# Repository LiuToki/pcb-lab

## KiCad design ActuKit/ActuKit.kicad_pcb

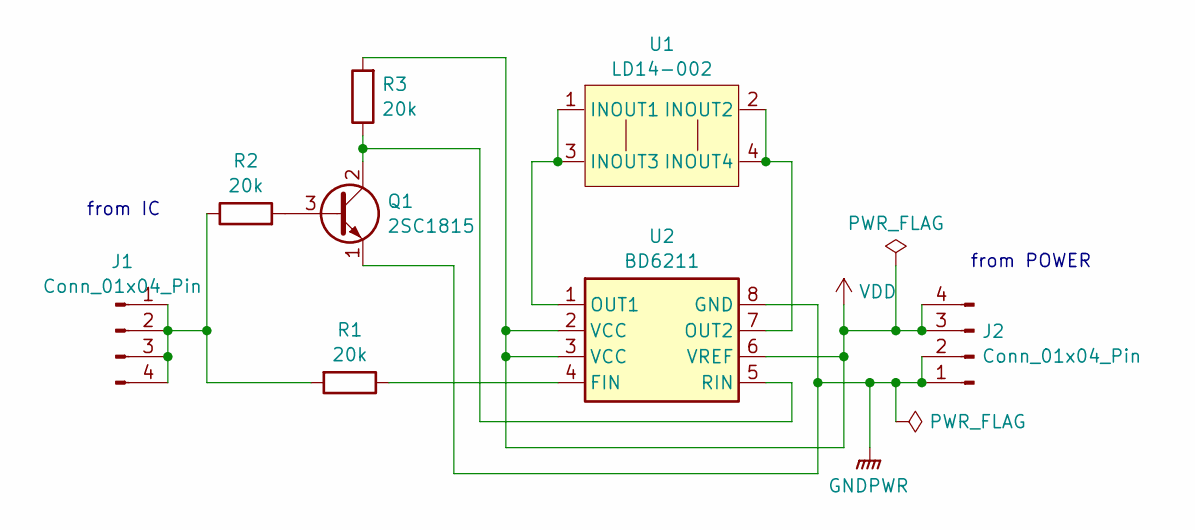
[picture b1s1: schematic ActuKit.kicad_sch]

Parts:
J1, J2: Conn_01x04_Pin; PinHeader_1x04_P2.54mm_Vertical
Q1: 2SC1815; TO-92_Inline
R1, R2, R3: 20k; R_Axial_DIN0204_L3.6mm_D1.6mm_P7.62mm_Horizontal
U1: LD14-002
U2: BD6211; SOP-8_5.28x5.23mm_P1.27mm

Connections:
GNDPWR: J2.1, J2.2, Q1.1 (E), U2.8 (GND)
unnamed: J1.1, J1.2, J1.3, J1.4, R1.2, R2.1
unnamed: Q1.3 (B), R2.2
unnamed: Q1.2 (C), R3.1, U2.5 (RIN)
unnamed: U1.1 (INOUT1), U1.3 (INOUT3), U2.1 (OUT1)
unnamed: U1.2 (INOUT2), U1.4 (INOUT4), U2.7 (OUT2)
unnamed: R1.1, U2.4 (FIN)
VDD: J2.3, J2.4, R3.2, U2.2 (VCC), U2.3 (VCC), U2.6 (VREF)

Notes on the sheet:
from IC
from POWER

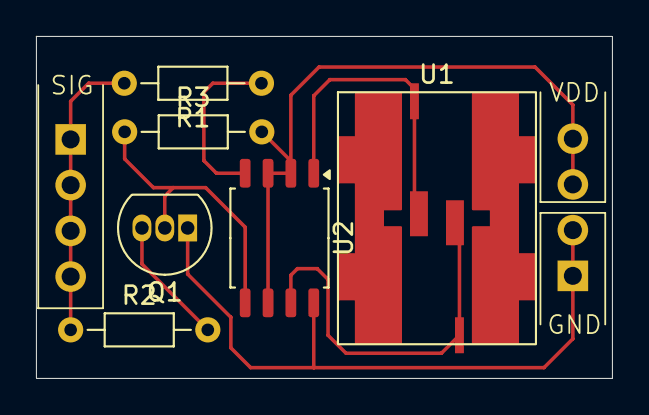
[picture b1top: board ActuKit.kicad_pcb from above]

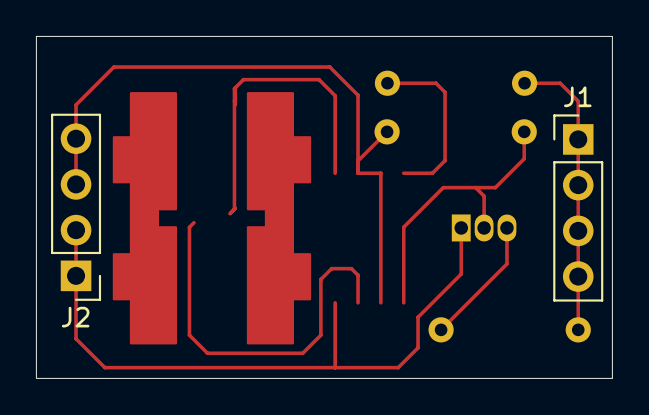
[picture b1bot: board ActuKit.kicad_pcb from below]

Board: 2 copper layers, 32.0 x 19.0 mm, 8 parts (2 on the bottom side), 8 nets.

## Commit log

2024-12-07 Add Submodule
    [Add] liut-kicad-library
2024-12-07 [ActuKit] Add Project
2024-12-07 Change the name of LICENSE
2024-12-07 ライブラリの参照を更新
2024-12-07 [ActuKit] 基板の作成
2024-12-07 [ActuKit] Add gerber data
2024-12-22 [ActuKit] 基板動作用サンプルプログラムを追加
2024-12-22 [ActuKit] ミルピンのガイド用シルクの追加
2024-12-22 [ActuKit] LD14-002のライブラリ更新に合わせた基板の変更
